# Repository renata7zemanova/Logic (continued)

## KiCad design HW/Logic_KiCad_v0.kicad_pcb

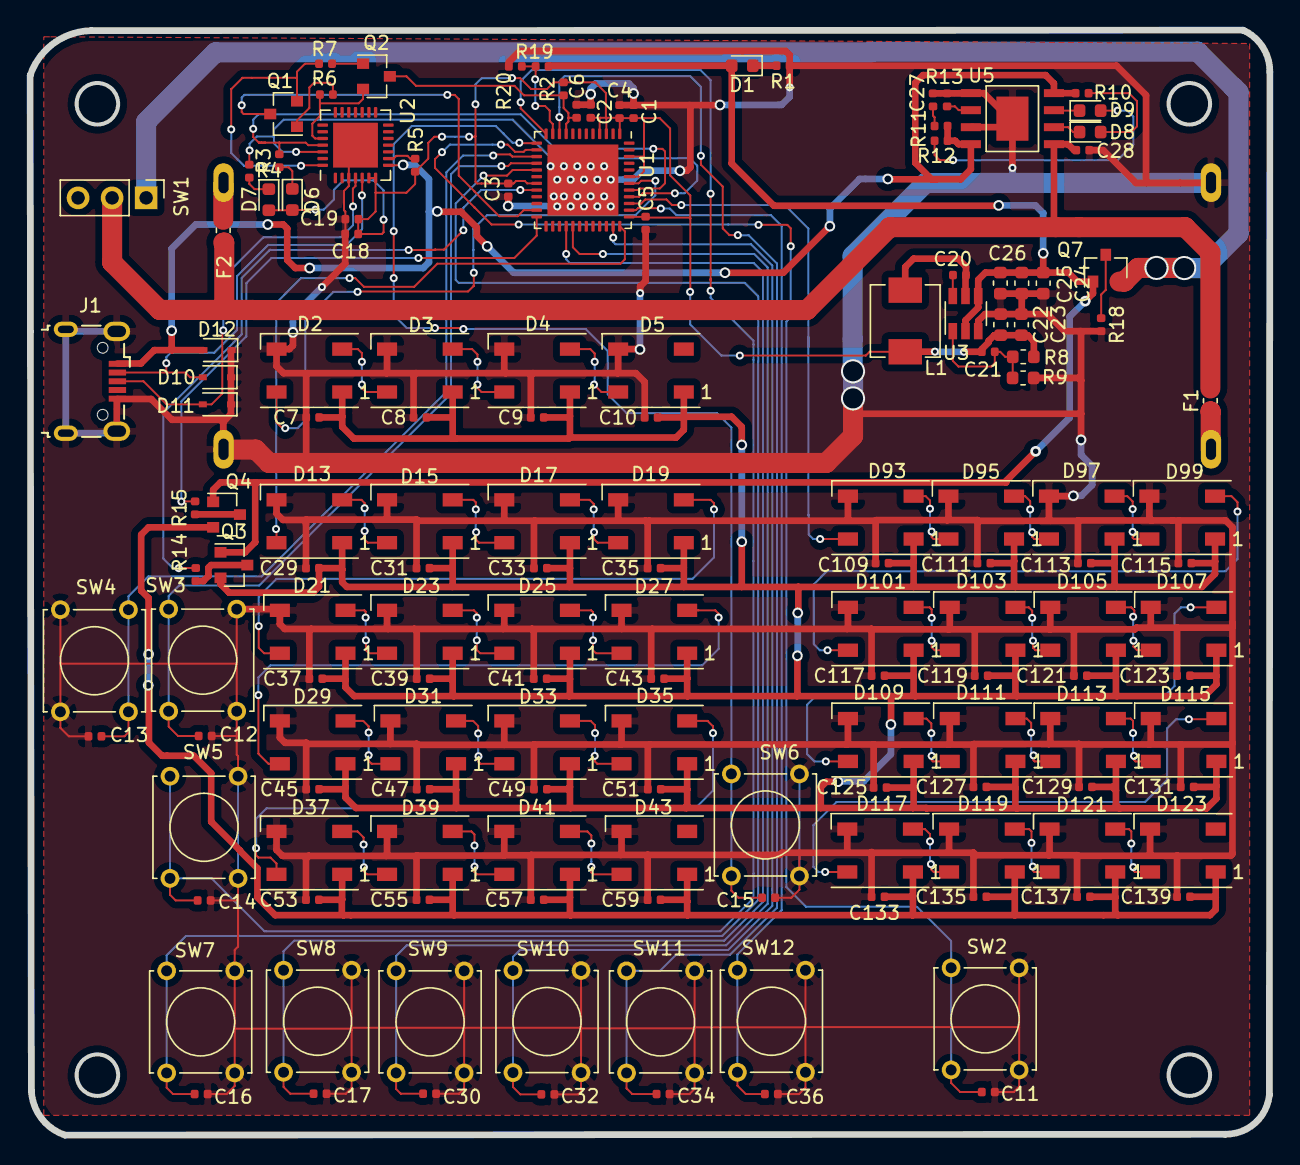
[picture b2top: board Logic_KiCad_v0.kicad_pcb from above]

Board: 2 copper layers, 92.5 x 82.5 mm, 152 parts (1 on the bottom side), 86 nets.

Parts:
C1, C27, C28: 10u; C_0402_1005Metric
C2, C3, C4, C5, C6, C7, C8, C9, C10, C19, C20, C29, C31, C33, C35, C37, C39, C41, C43, C45, C47, C49, C51, C53, C55, C57, C59, C109, C111, C113, C115, C117, C119, C121, C123, C125, C127, C129, C131, C133, C135, C137, C139: 100n; C_0402_1005Metric
C11, C12, C13, C14, C15, C16, C17, C30, C32, C34, C36: 10n; C_0402_1005Metric
C18: 4u7; C_0402_1005Metric
C21: 47p; C_0402_1005Metric
C22, C23, C24, C25, C26: 22u; C_0603_1608Metric
D1, D6, D7, D8: green; LED_0603_1608Metric
D2, D3, D4, D5, D13, D15, D17, D19, D21, D23, D25, D27, D29, D31, D33, D35, D37, D39, D41, D43, D93, D95, D97, D99, D101, D103, D105, D107, D109, D111, D113, D115, D117, D119, D121, D123: WS2812B; LED_WS2812B_PLCC4_5.0x5.0mm_P3.2mm
D9: red; LED_0603_1608Metric
D10, D11, D12: SD05_SOD323; D_SOD-323
F1, F2: Polyfuse; Fuse_0603_1608Metric
J1: USB_B_Micro; USB_Micro-B_Wuerth_629105150521
L1: 4u7; MWSA0503S
Q1, Q2: Q_NPN_BEC; SOT-23
Q3, Q4, Q7: Q_PMOS_SDG; SOT-23
R1, R2, R6, R7, R14, R15, R18, R20: 10k; R_0402_1005Metric
R3, R4: 47k; R_0402_1005Metric
R5, R13: 2k; R_0402_1005Metric
R8: 160k; R_0603_1608Metric
R9: 36k; R_0603_1608Metric
R10, R12: 1k; R_0402_1005Metric
R11: 1; R_0402_1005Metric
R19: 39k; R_0402_1005Metric
SW1: SW_SPDT; PinHeader_1x03_P2.54mm_Vertical
SW2, SW3, SW4, SW5, SW6, SW7, SW8, SW9, SW10, SW11, SW12: button; SW_Tactile_Straight_KSL0Axx1LFTR
U1: ESP32-PICO-D4; QFN-48-1EP_7x7mm_P0.5mm_EP5.3x5.3mm
U2: CP2102N-A01-GQFN28; QFN-28-1EP_5x5mm_P0.5mm_EP3.35x3.35mm
U3: SY8105; TSOT-23-6
U4: Dual_battery; battery_dock
U5: TP4056

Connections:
+3V3: C1.2, C2.1, C3.2, C4.1, C5.2, C18.2, C19.2, C21.2, C22.2, C23.2, D6.2, D7.2, L1.2, R2.1, R5.1, R8.1, U1.1, U1.3, U1.4, U1.19, U1.37, U1.43, U1.46, U2.6, U2.7
/herni_LED.sch/2.sch/DATA_IN: D19.2, D21.4
/herni_LED.sch/3.sch/DATA_IN: D27.2, D29.4
/herni_LED.sch/4.ch/DATA_IN: D35.2, D37.4
/hodnoceni_LED.sch/2.sch/DATA_IN: D99.2, D101.4
/hodnoceni_LED.sch/3.sch/DATA_IN: D107.2, D109.4
/hodnoceni_LED.sch/4.ch/DATA_IN: D115.2, D117.4
BARVA_1: C16.2, SW7.1, U1.17
BARVA_2: C17.2, SW8.1, U1.28
BARVA_3: C30.2, SW9.1, U1.29
BARVA_4: C32.2, SW10.1, U1.35
BARVA_5: C34.2, SW11.1, U1.10
BARVA_6: C36.2, SW12.1, U1.38
BTN_END: C12.2, SW3.1, U1.16
BTN_ENTER: C11.2, SW2.1, U1.14
BTN_NEW_GAME: C13.2, SW4.1, U1.15
BTN_SIPKA_VLEVO: C14.2, SW5.1, U1.12
BTN_SIPKA_VPRAVO: C15.2, SW6.1, U1.13
D+: D11.2, J1.3, U2.4
D-: D10.2, J1.2, U2.5
DATA_herni_LED: D13.4, U1.36
DATA_hodnoceni_LED: D93.4, U1.39
DATA_zadani_LED: D2.4, U1.42
EN: C6.2, Q2.3, R2.2, U1.9
GND: C1.1, C2.2, C3.1, C4.2, C5.1, C6.1, C7.2, C8.2, C9.2, C10.2, C11.1, C12.1, C13.1, C14.1, C15.1, C16.1, C17.1, C18.1, C19.1, C22.1, C23.1, C24.2, C25.2, C26.2, C27.2, C28.2, C29.2, C30.1, C31.2, C32.1, C33.2, C34.1, C35.2, C36.1, C37.2, C39.2, C41.2, C43.2, C45.2, C47.2, C49.2, C51.2, C53.2, C55.2, C57.2, C59.2, C109.2, C111.2, C113.2, C115.2, C117.2, C119.2, C121.2, C123.2, C125.2, C127.2, C129.2, C131.2, C133.2, C135.2, C137.2, C139.2, D2.3, D3.3, D4.3, D5.3, D10.1, D11.1, D12.1, D13.3, D15.3, D17.3, D19.3, D21.3, D23.3, D25.3, D27.3, D29.3, D31.3, D33.3, D35.3, D37.3, D39.3, D41.3, D43.3, D93.3, D95.3, D97.3, D99.3, D101.3, D103.3, D105.3, D107.3, D109.3, D111.3, D113.3, D115.3, D117.3, D119.3, D121.3, D123.3, J1.5, J1.6, R1.1, R9.2, R13.2, R18.2, R20.2, SW2.2, SW3.2, SW4.2, SW5.2, SW6.2, SW7.2, SW8.2, SW9.2, SW10.2, SW11.2, SW12.2, U1.49, U2.3, U2.29, U3.3, U4.2, U4.4, U5.1, U5.3, U5.9
IO0: Q1.3, U1.23
MERENI_BATERKY: R19.2, R20.1, U1.11
unnamed: C20.1, L1.1, U3.5
unnamed: C20.2, U3.6
unnamed: C21.1, R8.2, R9.1, U3.1
unnamed: C27.1, R11.2
unnamed: D1.1, R1.2
unnamed: D2.2, D3.4
unnamed: D3.2, D4.4
unnamed: D4.2, D5.4
unnamed: D6.1, R3.1
unnamed: D7.1, R4.1
unnamed: D8.1, U5.6
unnamed: D8.2, R10.1
unnamed: D9.1, U5.7
unnamed: D9.2, R12.1
unnamed: D13.2, D15.4
unnamed: D15.2, D17.4
unnamed: D17.2, D19.4
unnamed: D21.2, D23.4
unnamed: D23.2, D25.4
unnamed: D25.2, D27.4
unnamed: D29.2, D31.4
unnamed: D31.2, D33.4
unnamed: D33.2, D35.4
unnamed: D37.2, D39.4
unnamed: D39.2, D41.4
unnamed: D41.2, D43.4
unnamed: D93.2, D95.4
unnamed: D95.2, D97.4
unnamed: D97.2, D99.4
unnamed: D101.2, D103.4
unnamed: D103.2, D105.4
unnamed: D105.2, D107.4
unnamed: D109.2, D111.4
unnamed: D111.2, D113.4
unnamed: D113.2, D115.4
unnamed: D117.2, D119.4
unnamed: D119.2, D121.4
unnamed: D121.2, D123.4
unnamed: F1.1, U4.1
unnamed: F2.1, U4.3
unnamed: Q1.1, R6.1
unnamed: Q1.2, R7.2, U2.28
unnamed: Q2.1, R7.1
unnamed: Q2.2, R6.2, U2.24
unnamed: Q3.3, R14.1
unnamed: Q4.3, R15.1
unnamed: Q7.3, R18.1
unnamed: R5.2, U2.9
unnamed: R13.1, U5.2
RX_ESP: R4.2, U1.40, U2.26
TX_ESP: R3.2, U1.41, U2.25
VBUS: D12.2, J1.1, R10.2, R11.1, R12.2, U2.8, U5.4, U5.8
V_BAT: C24.1, C25.1, C26.1, D1.2, Q3.1, Q4.1, Q7.1, R19.1, U3.2, U3.4
V_BAT_1: C7.1, C8.1, C9.1, C10.1, C29.1, C31.1, C33.1, C35.1, C37.1, C39.1, C41.1, C43.1, C45.1, C47.1, C49.1, C51.1, C109.1, C111.1, C113.1, C115.1, C117.1, C119.1, C121.1, C123.1, C125.1, C127.1, C129.1, C131.1, D2.1, D3.1, D4.1, D5.1, D13.1, D15.1, D17.1, D19.1, D21.1, D23.1, D25.1, D27.1, D29.1, D31.1, D33.1, D35.1, D93.1, D95.1, D97.1, D99.1, D101.1, D103.1, D105.1, D107.1, D109.1, D111.1, D113.1, D115.1, Q3.2
V_BAT_2: C53.1, C55.1, C57.1, C59.1, C133.1, C135.1, C137.1, C139.1, D37.1, D39.1, D41.1, D43.1, D117.1, D119.1, D121.1, D123.1, Q4.2
V_BAT_PRIME: C28.1, F1.2, F2.2, SW1.2, U5.5
V_BAT_SPINANE: Q7.2, SW1.1
ZAPINANI_1_CAST_LED: R14.2, U1.20
ZAPINANI_2_CAST_LED: R15.2, U1.24

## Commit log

2020-09-28 PCB: game controls, USB to 232, stepdown for ESP, battery pack
2020-09-28 add "citace" to gitignore
2020-09-28 add charger
2020-09-28 change gitignore, add symbols.lib
2020-09-30 add power supply for ESP, erase resistors by buttons, add power supply for CP2102, add communication control (CP2102-ESP)
2020-09-30 change USB
2020-09-30 changed switching power supply for LEDs
2020-09-30 change structure of LEDs, add switching power supply of LEDs in parts
2020-09-30 remove pin from USB
2020-10-01 add some packages
2020-10-01 add polyfuse for battery, remove resistor by SY8105, fix mistake by charger
2020-10-01 add reverse polarity protection
2020-10-01 add capacitor to power of ESP
2020-10-01 add measurement voltage on batteries
2020-10-01 fix mistake
2020-10-01 cleanup
2020-10-02 new battery pack schematic
2020-10-02 add some codes for JLCPCB, change package and schematic of CP2102
2020-10-02 add some codes for JLCPCB
2020-10-03 add footprint of battery pack
2020-10-03 remove unused schematic
2020-10-03 add footprint of inductor, add codes for JLCPCB, repair mistakes
2020-10-04 numbering components, place components on board
2020-10-04 new position of some components
2020-10-04 repair package of TP4056
2020-10-05 start routing
2020-10-05 repair mistake with buttons
2020-10-05 rotate LEDs and capacitors
2020-10-05 make smaller test version, start routing
2020-10-06 continuation routing
2020-10-06 finishing routing, make fab
2020-10-08 ready for first prototype
2020-10-09 add mounting holes, repair gitignore
2020-10-09 update gitignore, add block schematic
2020-10-21 change structure of buttons, switching power
2020-11-05 start writing test, update gitignore
2020-11-05 start programming - testing HW
2020-11-11 continue programming
2020-11-11 update KiCad
2020-11-12 change path
2020-11-12 repair project
2020-11-12 repair some misakes from prototype
2020-11-12 add version and author
2020-11-15 repair mistake with tranzistors, repair programming ESP PICO
2020-11-15 deposit of DPS, start v1.0
2020-11-16 start place components
2020-11-16 change footprint of buttons, continue placing components, repair mistake in power voltage
2020-11-17 routing PCB
2020-11-18 add rounded corners PCB, place mounting holes
2020-11-18 repair footprint of P and N MOS, add order codes for JLCPCB, preparing for fab
2020-11-18 nicer routing
2020-11-19 writing text
2020-11-21 repair mistakes
2020-11-23 v1.0 for fab
2020-11-23 add back-up v1.0 for fab
2020-11-23 repair mistake in v1.0 - for fab, add to back-up v1.0 folder fab
2020-11-23 v1.0 for fab (for great success once again)
2020-11-25 Writing text (with mistake)
2020-11-25 add images (with mistakes)
2020-11-25 repair mistake
2020-11-26 writing text, add images
2020-11-30 repair mistakes, add images
2020-11-30 update gitignore
2020-12-17 text in semestral projekt
2021-01-01 programing Logic, 1. function version
2021-01-01 make presentation
2021-01-06 repair WS2812B na WS2812C
2021-01-06 make presentation about semestral project
2021-01-07 presentation for semestral project, repair picture with schemitics with LEDs WS2812C
2021-01-24 V1.1 change SMD buttons, add diode on VCC
2021-01-27 deposit of v1.1
2021-01-27 deposti v1.1 (repair mistake)
2021-02-25 add level shifter
2021-02-25 add DIPS
2021-03-15 repair footprint of DIP and USB micro, change buttons with higher fretboard
2021-03-15 change USB footprint, add 3. DIP
2021-03-16 repair DIPs, add pullup and pulldown resistors
2021-03-22 add tooling holes
2021-03-23 move mounting holes, move power LED 3V3
2021-03-24 update rotation of components for fab, update folder fab
2021-03-30 Version 1.2 for fab
2021-04-07 make code readeble, add delete colors, repair mistake with press btn end and position of cursors
2021-04-07 design of box
2021-04-07 make code better
2021-04-08 make new functions for readeble code
2021-04-08 functions are in new file (lib.h)
2021-04-08 add game on 3 colors
2021-04-08 add some functions for readeble code
2021-04-08 add some functions, rename functions
2021-04-19 some changes in box (test)
2021-04-19 save everything for work
2021-04-19 test commit
2021-04-19 change template for text bachelor thesis
2021-04-19 change template, repair mistakes with name of files
2021-04-19 change template for oneside print
2021-04-22 writing text, start writing part about software
2021-04-28 make schematic beautiful (for printing)
2021-04-29 change and edit images in text, edit the size of images
2021-04-29 update images
2021-04-29 make exports from schematics
2021-05-02 repair template
2021-05-02 update text
2021-05-05 repair top of box
2021-05-07 repair roof, add hole for switch
2021-05-07 add citation
2021-05-08 edit box
2021-05-09 add programming switches
2021-05-09 add anotation, keywords
2021-05-10 repair mistakes with power supply switching
2021-05-10 sides of roof are wider, bigger hole for nut, add elevation for roof
2021-05-10 add text about switch on power supply
2021-05-11 make hole for buttons bigger, add texts, make hole for USB connectors bigger
2021-05-11 repair mistake with cursor in evaluate
2021-05-13 add diagrams to text
2021-05-13 repair texts on box
2021-05-13 repair texts on box (bigger space)
2021-05-13 repair some sentences beginning with shortcut
2021-05-17 add fixed spaces in text, translate contents in table, storhcuts to words
2021-05-18 repair board for printing
2021-05-18 add image of whole PCB
2021-05-18 new support of PCB
2021-05-19 add instructions for Elektrikarium, delete list of extract
2021-05-19 label of tabel align left, repair generation last attachment (instructions for Elektrikarium)
2021-05-19 add thanks
2021-05-21 add fixed spaces
2021-05-21 repair box for SLA 3D printing, add colors
2021-05-26 repair hole for power switch
2021-05-26 repair small mistakes
2021-05-26 add text about 3D printing SLA
2021-05-28 generate new STL for final printing box
2021-05-30 add photos, instructions, box and PCB
2021-05-30 repair mistakes in text
2021-05-31 repair last mistakes, final text
2021-05-31 update readme - add about switch position
2021-05-31 add link
2021-05-31 repair link
2021-06-01 final text
2021-06-13 add answer to the question from opponent
2021-06-14 final presentation
2021-07-07 new version of box
